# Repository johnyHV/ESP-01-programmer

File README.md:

# ESP-01-programmer version 1.0
Programmer for module ESP-01

If do you see in Arduino IDE console text "Connecting" then, switch GPIO0 pin to ground, ant push RESET button. 
After sucessfully upload source code to module ESP-01 please disconnect GPIO0 pin from ground, and push RESET button. 
After this step is surce code uploaded in MCU.

# ESP-01 module

# USB to UART converter
Do you need this USB to UART converter, but please logic level you must set to 5V

# Schematic

# Programmer board

# Prototype version

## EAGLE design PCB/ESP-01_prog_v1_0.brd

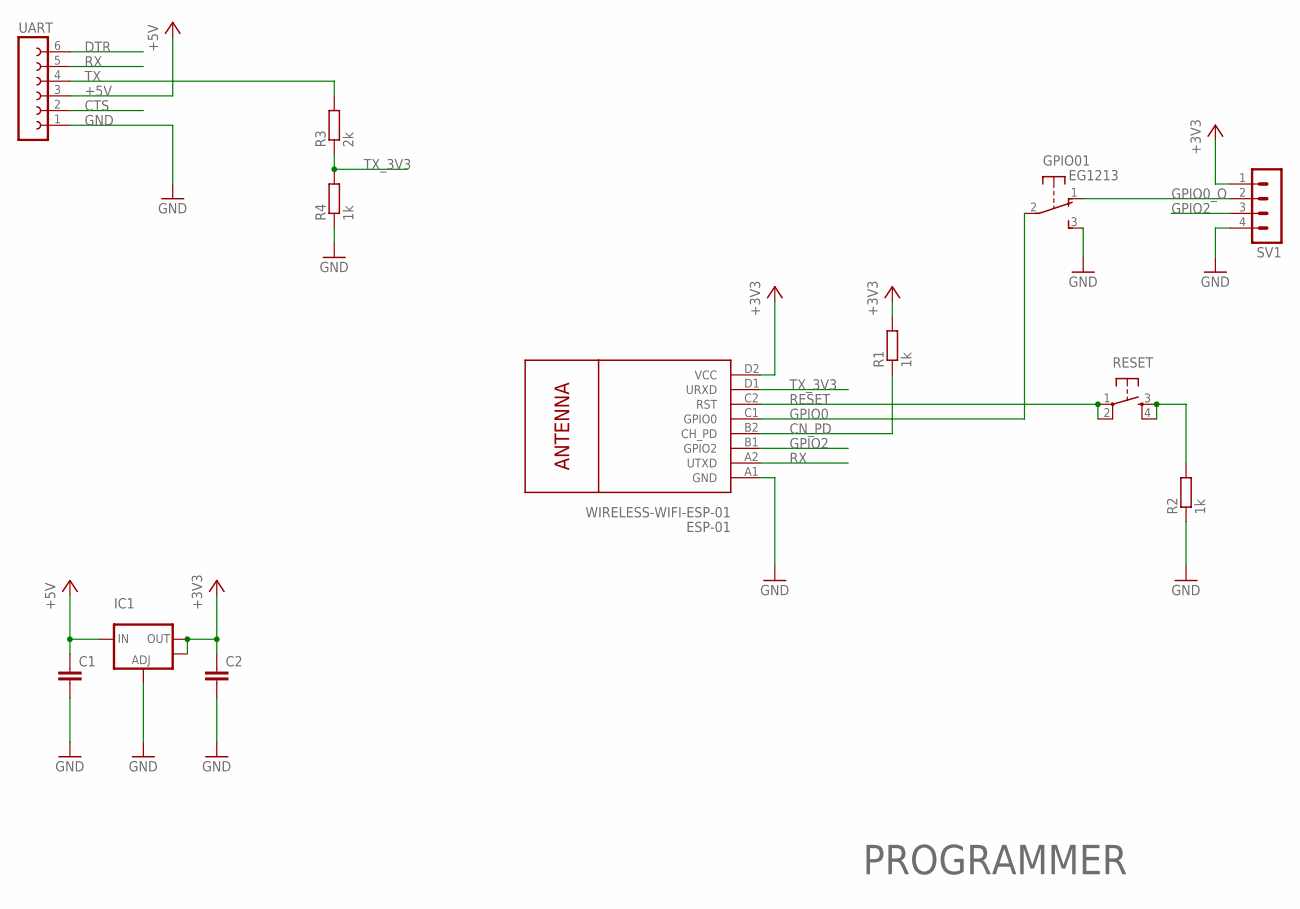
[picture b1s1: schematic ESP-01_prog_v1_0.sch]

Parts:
C1, C2: C-EUC0603; C0603
ESP-01: WIRELESS-WIFI-ESP-01
GPIO0: EG1213
IC1: LM1117SOT223; SOT223
R1, R2, R4: 1k; R0603
R3: 2k; R0603
RESET: TAC_SWITCHPTH; TACTILE-PTH
SV1: MA04-1
UART: FE06-1; FE06

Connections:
+3V3: C2.1, ESP-01.D2 (VCC), IC1.2 (OUT), IC1.4 (OUT), R1.2, SV1.1
+5V: C1.1, IC1.3 (IN), UART.3
CN_PD: ESP-01.B2 (CH_PD), R1.1
CTS: UART.2
DTR: UART.6
GND: C1.2, C2.2, ESP-01.A1 (GND), GPIO0.3 (S), IC1.1 (ADJ), R2.1, R4.1, SV1.4, UART.1
GPIO0: ESP-01.C1 (GPIO0), GPIO0.2
GPIO0_O: GPIO0.1 (O), SV1.2
GPIO2: ESP-01.B1 (GPIO2), SV1.3
unnamed: R2.2, RESET.3, RESET.4
RESET: ESP-01.C2 (RST), RESET.1, RESET.2
RX: ESP-01.A2 (UTXD), UART.5
TX: R3.2, UART.4
TX_3V3: ESP-01.D1 (URXD), R3.1, R4.2

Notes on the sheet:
PROGRAMMER

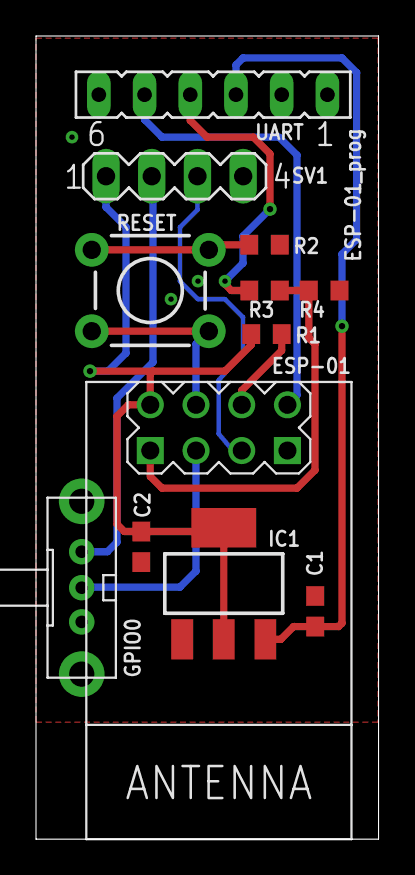
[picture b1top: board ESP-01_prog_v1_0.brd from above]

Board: 2 copper layers, 19.0 x 44.6 mm, 12 parts (0 on the bottom side), 12 nets.

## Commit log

2020-11-17 init

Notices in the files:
parts and their libraries:
SparkFun-Retired: Licensing: Creative Commons ShareAlike 4.0 International - https://creativecommons.org/licenses/by-sa/4.0
acs712: Released under the Creative Commons Attribution 4.0 International License: http://creativecommons.org/licenses/by/4.0
